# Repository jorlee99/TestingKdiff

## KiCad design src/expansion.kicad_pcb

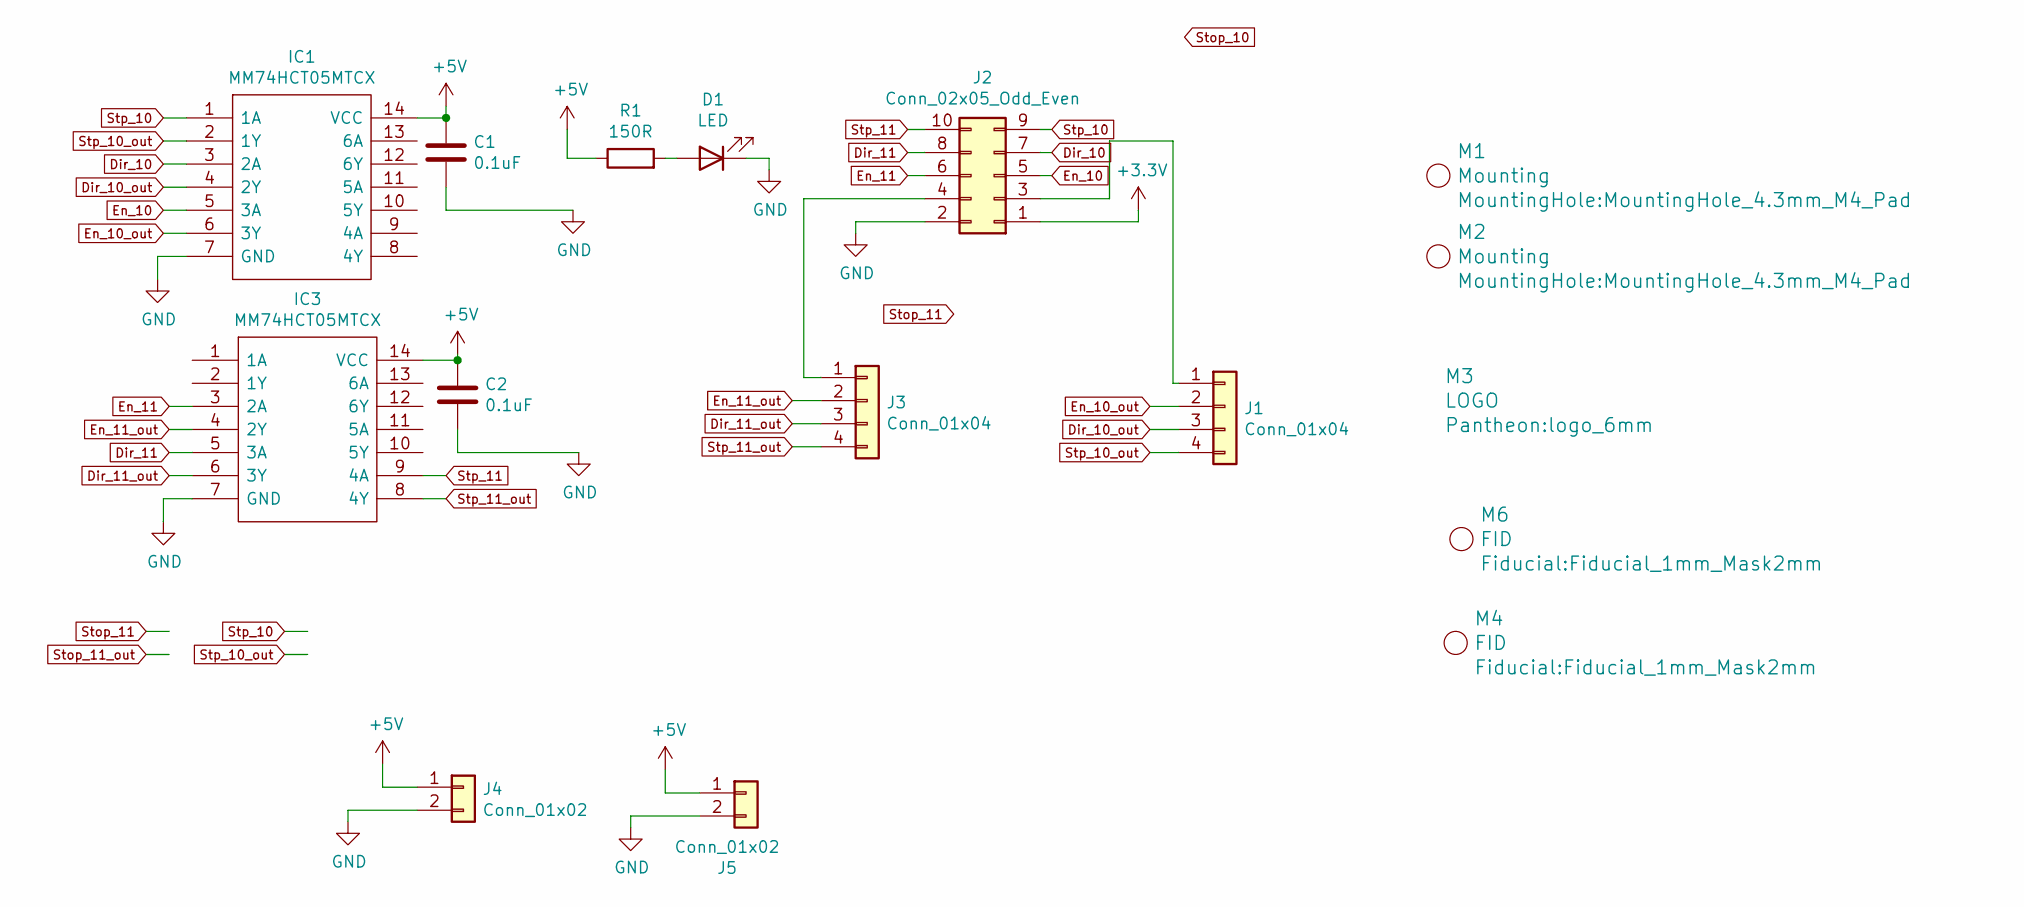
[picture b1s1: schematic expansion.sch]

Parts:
C1, C2: 0.1uF; C_0603_1608Metric_Pad1.05x0.95mm_HandSolder
D1: LED; LED_0603_1608Metric_Pad1.05x0.95mm_HandSolder
IC1, IC3: MM74HCT05MTCX; SOP65P640X120-14N; Manufacturer_Part_Number MM74HCT05MTCX
J1, J3: Conn_01x04; B04B-PASK-1
J2: Conn_02x05_Odd_Even; IDC_PIN_ARRAY_5x2
J4, J5: Conn_01x02; B02B-PASK-1LFSN
M1, M2: Mounting; MountingHole_4.3mm_M4_Pad
M3: LOGO; logo_6mm
M4, M6: FID; Fiducial_1mm_Mask2mm
R1: 150R; R_0603_1608Metric

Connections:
+3V3: J2.1
+5V: C1.1, C2.1, IC1.14 (VCC), IC3.14 (VCC), J4.1, J5.1, R1.1
Dir_10: IC1.3 (2A), J2.7
Dir_10_out: IC1.4 (2Y), J1.3
Dir_11: IC3.5 (3A), J2.8
Dir_11_out: IC3.6 (3Y), J3.3
En_10: IC1.5 (3A), J2.5
En_10_out: IC1.6 (3Y), J1.2
En_11: IC3.3 (2A), J2.6
En_11_out: IC3.4 (2Y), J3.2
GND: C1.2, C2.2, D1.1 (K), IC1.7 (GND), IC3.7 (GND), J2.2, J4.2, J5.2
unnamed: D1.2 (A), R1.2
unnamed: J1.1, J2.3
unnamed: J2.4, J3.1
Stp_10: IC1.1 (1A), J2.9
Stp_10_out: IC1.2 (1Y), J1.4
Stp_11: IC3.9 (4A), J2.10
Stp_11_out: IC3.8 (4Y), J3.4

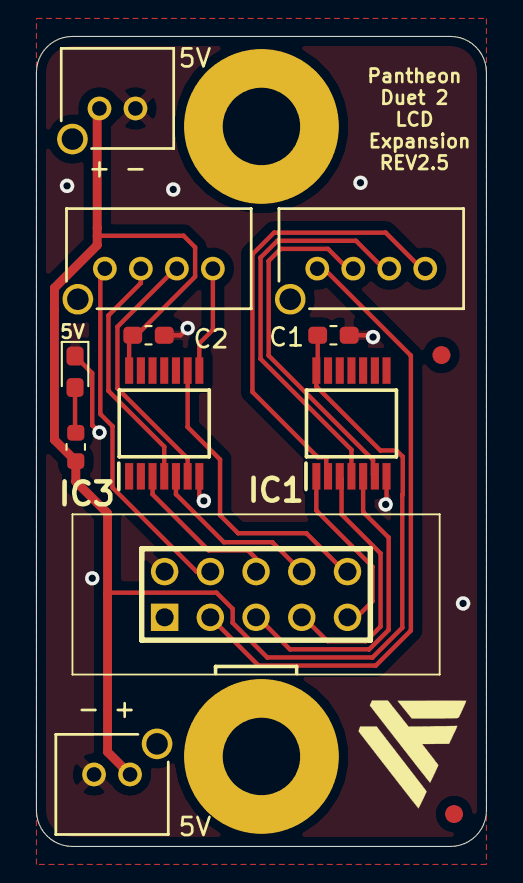
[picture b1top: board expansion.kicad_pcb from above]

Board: 2 copper layers, 25.0 x 45.0 mm, 16 parts (0 on the bottom side), 17 nets.

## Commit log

2021-05-28 Test Change

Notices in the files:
parts and their libraries:
Copyright 2016 Accelerated Designs. All rights reserved.
